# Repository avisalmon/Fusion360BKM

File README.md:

# Fusion360BKM

### Design a whole product with an AI that drives Fusion 360 for you: 3D parts, circuit boards a factory can make, and the case and production files that join them.

<!-- last-updated:start -->
**Last updated 20 November 2026** · 8 new lessons · [See what's new](docs/lessons_log.md)
<!-- last-updated:end -->

**Start page (Hebrew / English): https://avisalmon.github.io/Fusion360BKM/**

---

**Autodesk Fusion 360** is free for personal use and does 3D parts, electronics (schematics and boards) and the
fitting of one into the other. This repo is the best known method for working it **from a chat**: a small add-in
(`CopilotBridge`) runs inside Fusion and takes Python scripts over a local HTTP port; the AI in your editor writes
the script, runs it, reads back every body's measurements and a screenshot, and tells you what it sees. You keep
Fusion open beside the chat and watch the part appear.

Open the repo in VS Code with **Claude Code** or **GitHub Copilot** (Agent mode), type **"Tell me what to do"**
(or **"תגיד לי מה לעשות"**), and the chat:

* checks your computer and links the add-in into Fusion (one Fusion restart, once),
* asks what you want to make, writes a numbered spec in millimetres, and gets your OK,
* builds it in Fusion step by step, **verifying by numbers and by eye** after every run,
* exports STL for the printer, STEP for other CAD tools, F3D to keep,
* teaches as it goes, in Hebrew or English, and resumes where you stopped next time,
* pulls the newest version of this guide at the start of every session.

## Four stages

1. **Set up** (you, by hand): install [Fusion 360](https://www.autodesk.com/products/fusion-360/personal) and sign
   in; install [VS Code](https://code.visualstudio.com), [Git](https://git-scm.com/downloads), and an AI chat
   (Claude Code, or GitHub Copilot in Agent mode); in VS Code **Ctrl+Shift+P** -> **Git: Clone** -> paste
   `https://github.com/avisalmon/Fusion360BKM.git` -> **Open**. Every click: [docs/get_started.md](docs/get_started.md).
2. **Learn by hand, old school**: Avi Salmon's Fusion 360 course at
   [Babook](https://babook.co.il/courses/fusion360/) (Hebrew, seven video lessons: a coin, tweezers, a key, a
   vacuum-cleaner nozzle, a mug). Optional; the chat suggests the lesson that matches what you are about to build.
3. **The AI magic** (this repo): in the chat, type `Tell me what to do` / `תגיד לי מה לעשות`. The whole road is
   [docs/journey_checklist.md](docs/journey_checklist.md).
4. **Examples**: [examples/](examples/README.md), each with its scripts, files, pictures, what was verified, and what it
   taught this guide: [a box from a paper note](examples/06_sketched_box/README.md), three circuit boards, and the demo
   product below.

## Three tracks (and a fourth coming)

* **3D parts**: from words, a hand sketch or a real object, to a spec in mm, a script, checks, and STL to print.
* **Circuit design**: the circuit in words, a schematic, a placement *you* review, routing, then three layers of
  checks (Fusion's, ours against JLCPCB's limits, a simulated factory that reads the Gerbers) and one summary page
  per board with the zip to upload. Boards [10](examples/10_led_switch_board/index.html),
  [11](examples/11_blinker_555/index.html), [12](examples/12_tiny_arcade/index.html).
* **A whole product**: the board in 3D (every part's model comes from the library), a case designed around it and
  proven by intersecting every printed part with every part, screw, battery and cable, and a production package:
  STL, Gerbers, the assembly as STEP and `.f3d`, assembly steps, one bill of materials for everything. The demo:
  **[Tiny Arcade](examples/12_tiny_arcade/index.html)**, an ESP32 game board in a rounded handheld with a power
  bank inside (an example for learning, not for production).
* **Software** (coming later): the code that runs on the board, as part of the product.

## The part library

**[library/](library/index.html)**: real parts from a real shelf, each a full library cell (photos, pins checked on
the part, a footprint and symbol checked in Fusion, a 3D model). Every user keeps their own; Avi's is public, as the
example of what a library should look like. **Take one, give back two:** borrow a part from Avi's shelf today
instead of waiting for AliExpress, and order two that come back to him.

## What's in the box

```
index.html                 The start page (GitHub Pages), Hebrew + English
CLAUDE.md                  The AI's standing rules for this repo
.claude/skills/            9 playbooks: design-with-fusion, setup-fusion-bridge, fusion-modeling, fusion-files,
                           sketch-to-design, fusion-mentor, fusion-electronics, build-example, publish-to-github
.github/skills/            The same playbooks for GitHub Copilot (generated, kept identical by a test)
.github/copilot-instructions.md, AGENTS.md   Generated instructions + an index of every skill
CopilotBridge/             The Fusion add-in: HTTP server + helpers in millimetres (sketch, extrude, revolve,
                           fillet, shell, holes, patterns, parameters, export, screenshot)
scripts/fusion.py          One tool: doctor | install | launch | ping | new | run | exec | info | shot | export | dialog
scripts/fusion_dialog.ps1  Reads and clicks Fusion's modal dialogs when they block the bridge
templates/parametric_box/  A known-good start: a shelled box with a lid, eight parameters, verified
examples/                  Built from the chat, with evidence: 06_sketched_box (from a paper note); boards
                           10, 11 and 12; 12_tiny_arcade is a whole product with its production package
library/                   The part library: one folder per owner, one per part; index.html is its page
                           (scripts/library_page.py)
my_designs/                YOUR work (git-ignored, so updates never touch it)
exports/                   STL / STEP / F3D / PNG output (git-ignored)
docs/                      Setup, the journey, architecture, the Fusion reference, procedures, gotchas, what's new
```

## By hand, without the AI

```powershell
python scripts\fusion.py doctor                             # what is there, what is missing, the next command
python scripts\fusion.py install                            # link the add-in into Fusion (then restart Fusion once)
python scripts\fusion.py launch                             # start Fusion and wait for the bridge
python scripts\fusion.py ping                               # {"fusion": "2706.1.14", "bridge": "0.1.1", "doc": ...}
python scripts\fusion.py run templates\parametric_box\design.py
python scripts\fusion.py shot exports\box.png               # a picture of the viewport
python scripts\fusion.py new my_part                        # my_designs\my_part\design.py from the template
python scripts\fusion.py export my_part                     # STL (per body + whole), STEP, F3D into exports\
```

`scripts/fusion.py` needs only Python's standard library. The repo's own checks (`pytest`, `ruff`) use a virtualenv:
`python -m venv env` then `.\env\Scripts\python.exe -m pip install -r requirements-dev.txt`.

**What the setup is, in one paragraph.** Fusion must be running (minimised is fine) and signed in. The add-in is
linked into Fusion's AddIns folder and starts with Fusion; it listens on `127.0.0.1:8787` only. The chat sends a
Python script, the add-in runs it on Fusion's main thread, and sends back printed output, a `result` value and any
traceback. It is not an MCP server (a thin MCP wrapper over the same calls is possible later). A modal dialog in
Fusion blocks everything until somebody clicks it; `fusion.py dialog` can. Details: [docs/architecture.md](docs/architecture.md).

## Honest status

Tested on Windows 11 with Fusion 2706.1.14: `doctor`, `install` (as a junction), `launch` (a cold start, bridge up
in 35 s), `ping`, the template built through the bridge with its measurements read back and its screenshot
described, exports (STL, STEP, F3D), opening `.f3d` / STEP / STL, editing an opened design's timeline, and clearing
the update and *Active Sessions* dialogs. The first example is real: a hand-drawn paper note became a verified tray
in one run ([examples/06_sketched_box](examples/06_sketched_box/README.md)). The repo checks itself (ruff, tests,
skills in sync) and CI has been green on every push; the start page is served at the Pages URL above. Not yet: the
course's five examples, electronics, a printed part, a fresh clone on another computer, GitHub Copilot end to end,
macOS. See [docs/blueprint_roadmap.md](docs/blueprint_roadmap.md) and [docs/backlog.md](docs/backlog.md).

## License

[MIT](LICENSE). Use it, change it, teach with it.

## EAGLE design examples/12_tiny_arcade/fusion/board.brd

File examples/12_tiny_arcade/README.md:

# 12 Tiny Arcade: a game board from the owner's own parts, then its 3D model and its box

The Single Button kit ([SingleButtonKitBKM](https://github.com/avisalmon/SingleButtonKitBKM): an ESP32, a
0.96 inch screen, a button and a buzzer on a breadboard) as a small circuit board with six buttons: A, B and
a direction pad. Every part comes from the owner's library ([library/avi_salmon](../../library/README.md)),
real parts from his store with their pins confirmed on the part. The kit's pins are kept, so its programs
(Flappy) run unchanged. One flow: **board, then the board in 3D, then a 3D-printed box**, with two reviews
by the owner: the placement, and the printing concept.

Status: in progress. The board is done: the owner's placement (2026-11-19), routed on two layers with no
vias; Fusion's checks, our checks and the simulated factory all pass with 0 errors; the factory files are made
([summary page](index.html)). The board is in 3D, each part from its library model. The case (a rounded
handheld, the power bank inside, the board open on top) is agreed by the owner, and its production package is
made: STL files to print, the design (.f3d), the assembly (.step) with its screws and its cable, a true-size
paper template, assembly steps, and a bill of materials for everything (2026-11-20). **An example for learning,
not made for production** (the owner's word): it is not printed or ordered, and the bank is the owner's size,
100 x 70 x 15 mm.

| Part | Pin on the ESP32 | Note |
|---|---|---|
| screen SCL / SDA, VCC, GND | G22 / G21, 3V3, GND | the kit's pins |
| buzzer + / - | G23 / GND | the kit's pin |
| A, B | G4, G13 | A is the kit's one button |
| UP, DOWN, LEFT, RIGHT | G33, G26, G25, G32 | chosen so the four tracks reach the direction pad without crossing |

Each button's other contact goes to GND; the program turns on the pin's internal pull-up (released 1,
pressed 0), so there are no resistors. Pins avoided: 0, 2, 5, 12, 15 (they decide how the ESP32 starts),
1 and 3 (USB serial), 6-11 (flash), 34-39 (input only, no internal pull-up).

## Parts (the owner's library)

| Ref | Part | Library |
|---|---|---|
| U1 | ESP32 DevKitC, 38 pins | [esp32_devkitc_38](../../library/avi_salmon/esp32_devkitc_38/part.json) |
| DISP1 | OLED 0.96 inch, I2C, 4 pins | [oled_096_i2c](../../library/avi_salmon/oled_096_i2c/part.json) |
| BZ1 | buzzer TMB12A03 | [buzzer_tmb12a03](../../library/avi_salmon/buzzer_tmb12a03/part.json) |
| SW1-SW6 | tact switch 6 x 6 mm | [tact_switch_6x6](../../library/avi_salmon/tact_switch_6x6/part.json) |

## Build

```powershell
python scripts\fusion.py run examples\12_tiny_arcade\circuit.py 300   # 1. schematic (new design)
python scripts\fusion.py run examples\12_tiny_arcade\board.py 300     # 2. outline, holes, placement; the owner reviews
python scripts\fusion.py run examples\12_tiny_arcade\route.py 300     # 2b. tracks, once the owner agrees
python scripts\fusion.py run examples\12_tiny_arcade\factory.py 600   # 3. Fusion's checks, save, export, Gerbers
python scripts\pcb_check.py examples\12_tiny_arcade\fusion\board.brd  # 4. our board check, no Fusion needed
python scripts\factory_check.py examples\12_tiny_arcade\factory       # 5. the simulated factory
python scripts\fusion.py run examples\12_tiny_arcade\board3d.py 300   # 6. the board in 3D, the parts on it
python scripts\fusion.py run examples\12_tiny_arcade\case.py 900      # 7. the case, its checks, the production files
python scripts\board_summary.py examples\12_tiny_arcade              # 8. the summary page: board, case, production
```

The first placement proposal, then the owner's (a console: A and B left, the screen in the middle, the
direction pad right), then the routed board: top copper red, bottom blue.

The board in 3D, each part built from the model in its library record (boxes and cylinders, every size
with its source):

## The case (`case.py`)

The owner's brief (2026-11-20): rounded, modern, the power bank under the board, and the screen and buttons
left open so they are pressed and seen directly. Version 1 was a closed box with button caps; the owner
called it "too boxy", so it now lives only in git history. Version 2 is a rounded handheld, 140 x 82 mm and
21 mm thick to the deck, with the board on top (36 mm to the top of the buzzer). It is printed as two
parts, each flat and with no supports:

* **Body**: a rounded shell: corners of radius 30 seen from above, and a rounded bottom edge. The bank lies
  inside it, and ribs stop it sliding. The two ends are grips, so the thumbs land on A and B (left) and on
  the direction pad (right). A port bay in the left end shows the bank's ports and lights. It prints open
  side up.
* **Deck**: the lid. The board sits on four posts on it (4 x M3 x 8 from above, through the board's holes),
  inside a raised rim that guards its edges and is open at the ESP32's USB. Four M3 x 10 screws through the
  deck into columns in the grips hold the deck and the body together. It prints flat side down.

The bank sits 5 mm right of the centre, so the left grip has room for a short cable (10 cm): its USB-A plug in
the bank's left end, up through a slot in the deck, to the ESP32's micro-USB at the gap in the rim. The cable is
modelled too (blue in the pictures), so the fit check proves there is room for it. The port bay in the left end
reaches the bank's charging port and shows its lights.

The board, its parts and the bank are in the design as reference bodies, and the script intersects every
printed part with every one of them: all 0 mm3. Version 1 proved the check: a part moved 0.5 mm into
another gave exactly the expected volume.

### Production (`production/`, written by `case.py`)

| File | What it is |
|---|---|
| [tiny_arcade_case_body.stl](production/tiny_arcade_case_body.stl), [tiny_arcade_case_deck.stl](production/tiny_arcade_case_deck.stl) | the two printed parts, in mm, the right way up for the bed |
| [tiny_arcade_case.f3d](production/tiny_arcade_case.f3d) | the case's design in Fusion, the whole timeline (re-opened once to prove it: 8 components, 37 bodies) |
| [tiny_arcade_assembly.step](production/tiny_arcade_assembly.step) | the whole assembly (case, board, parts, bank, cable, the 8 screws) for any CAD program |
| [template_top_1to1.svg](production/template_top_1to1.svg) | the top at true size: print it on paper at 100 %, cut it out, hold it, try the buttons with your thumbs |
| [BOM.csv](production/BOM.csv) | everything to buy or make: the PCB, the 9 parts, the 2 printed parts, 8 screws, the bank, the cable |
| [production.json](production/production.json) | the assembly steps, the fit checks and the thumb distances, for the summary page |

Print in PLA, 0.2 mm layers, 4 walls, 20 % infill, no supports. Lay the body open side up and the deck flat side
down; both are already the right way up in the STL. Assembly (with the [exploded view](media/case_exploded.png)):
solder the board; screw it onto the deck (4 x M3 x 8); lay the bank in the body, ports to the left; screw the
deck onto the body (4 x M3 x 10, into the grips), the cable's far end through the deck's slot first; plug
it into the ESP32.

The thumbs: A and B sit 35-37 mm in from the left end; the direction pad's centre sits about 48 mm in from the
right end (LEFT 57 mm, RIGHT 39 mm). The pad is 11 mm further in from its end than A and B are from theirs, because
the board is centred in the case. Whether that is comfortable is for a hand to say: the paper template first.

## Status

| Step | Done |
|---|---|
| Parts: the owner's library, each part's symbol and footprint placed in Fusion and read back | 2026-11-19, Fusion 2706.1.17 |
| Schematic from the chat: 9 parts, 10 supply symbols, 11 nets; the netlist read back equal to the intent; looked at ([media/schematic.png](media/schematic.png)): no wire crosses another | 2026-11-19 |
| The ESP32's GND pins (the "power" kind, no wire) on the board's GND signal | 2026-11-19: pads 14, 20 and 26 read back in GND |
| Placement, first proposal: 86 x 64 mm, four M3 holes | 2026-11-19: placed and looked at ([media/placement_proposal.png](media/placement_proposal.png)) |
| Placement reviewed and moved by the owner in Fusion (a console layout), read back into `board.py`; B moved 1.5 mm off the corner screw, agreed | 2026-11-19 ([media/placement_owner.png](media/placement_owner.png)) |
| Routed (`route.py`): two layers, no vias; the direction pins swapped so no tracks cross (UP G33, DOWN G26, RIGHT G32) | 2026-11-19: 0 unrouted, no copper off the two layers, looked at ([media/board.png](media/board.png)) |
| Fusion's checks | 2026-11-19: board check 0 errors; ERC 5 findings, unused ESP32 input pins (EN, SVP, SVN, G34, G35), approved in `checks.json` with that reason, confirmed by the owner 2026-11-20 |
| Our board check (`pcb_check.py`) and the simulated factory (`factory_check.py`) | 2026-11-19, after a clean rebuild in a new design: 0 errors; the netlist equal to the intent; the bare-board e-test equal to the schematic (11 nets, no opens, no shorts). 2026-11-20: 0 warnings, once `pcb_check.py` learned that our library's parts carry their 3D model in part.json |
| Saved to the Fusion cloud (project "Tiny Arcade"), factory files | 2026-11-19 |
| The board in 3D, with the parts as 3D objects (`board3d.py`: each part's model from its library part.json, at its place on Fusion's 3D board) | 2026-11-19: built; each part's bounding box read back over its footprint; looked at ([media/board3d.png](media/board3d.png)). Heights above the board's underside: ESP32 8.7 mm (soldered straight on, 2026-11-20; it was 17.2 on female headers), buzzer 11.0, screen 6.6, buttons 6.5 (the 5 mm button is assumed): **to be measured** |
| The ESP32 soldered straight onto the board (no sockets), the owner's choice | 2026-11-20: `board3d.py` and `case.py` model it so; the ESP32's top is 7.2 mm above the board (from its model, not measured) |
| Printing concept: a power bank underneath, a short cable outside (the owner's direction); bank 100 x 70 x 15 mm (the owner's working size; the AliExpress listing's drawing says 93 x 63.5 x 14) | 2026-11-20 |
| The case, version 1 (a closed box, button caps) | 2026-11-20: built, 0 mm3 against every part; the owner: "too boxy" |
| The case, version 2 (`case.py`): a rounded handheld, the board open on top, the bank inside; body and deck | 2026-11-20: built in Fusion 2706.1.17; looked at from five views (media/case_v2*.png); **agreed by the owner** ("I like it"); the bank, the buttons, the screen and the buzzer are assumed sizes, **to be measured** |
| Production package (`production/`): STLs, .f3d (re-opened: 8 components, 37 bodies), .step, true-size template, BOM for everything, assembly steps, exploded view; the 8 screws and the cable modelled | 2026-11-20: 503 pairs intersected (printed parts and screw heads against everything, the cable included; shanks against the board and its parts): 0 mm3; the template rendered and looked at |
| The thumbs: comfortable to hold and press | measured on the model only (above); not tried by hand: an example, not printed |
| Printed, fitted | not planned: an example for learning (the owner, 2026-11-20) |

## What it taught this repo (so far)

* **Check what a command added, not only what it was asked to add.** Every ADD from a local library left
  one more copy of the part at the sheet's edge, which took the next name the script wanted. `sch_place`
  now ends the ADD (`EDIT .s1`) and fails if anything else appeared (gotcha 48).
* **Our check learned the supply pins**: an ESP32 pin named GND@14 of direction "pwr" joins GND with no
  wire; Fusion's board did, our check's schematic did not, so they disagreed. `pcb_check.py` now joins such
  pins by name, as EAGLE does.
* **Silkscreen stops short of the pads** in generated footprints (a square pad 1 reaches out to its corners).
* **One pin on two pads** (the tact switch's joined legs) and **GND pins that join by name**: the board's
  signal has them, the schematic's nets do not list them.

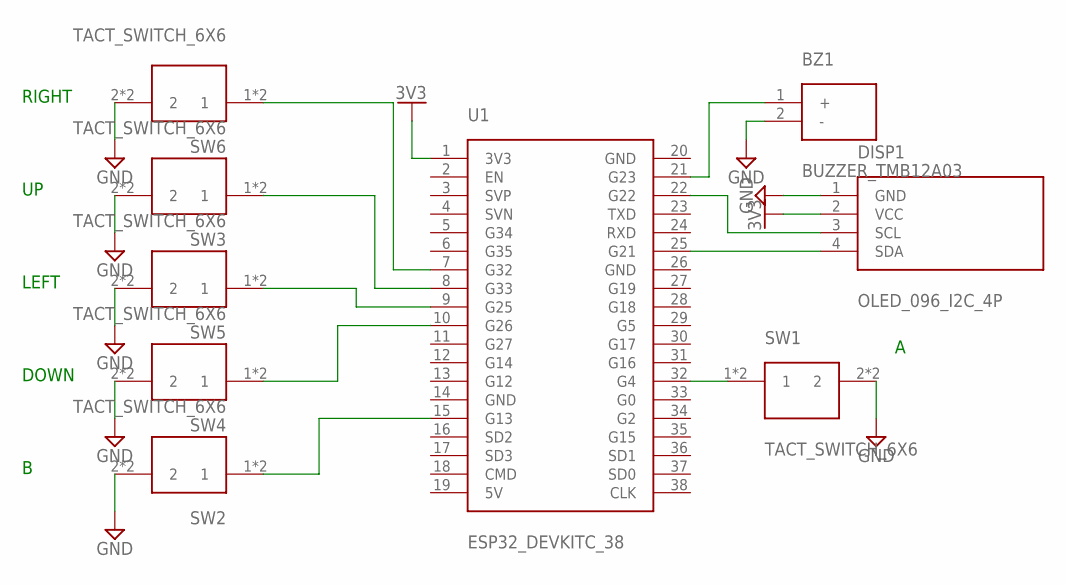
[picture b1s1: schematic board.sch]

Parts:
BZ1: BUZZER_TMB12A03
DISP1: OLED_096_I2C_4P
SW1, SW2, SW3, SW4, SW5, SW6: TACT_SWITCH_6X6
U1: ESP32_DEVKITC_38

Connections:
3V3: DISP1.2 (VCC), U1.1 (3V3)
BTN_A: SW1.1, SW1.3 (1), U1.32 (G4)
BTN_B: SW2.1, SW2.3 (1), U1.15 (G13)
BTN_DOWN: SW4.1, SW4.3 (1), U1.10 (G26)
BTN_LEFT: SW5.1, SW5.3 (1), U1.9 (G25)
BTN_RIGHT: SW6.1, SW6.3 (1), U1.7 (G32)
BTN_UP: SW3.1, SW3.3 (1), U1.8 (G33)
BUZZER: BZ1.1 (+), U1.21 (G23)
GND: BZ1.2 (-), DISP1.1 (GND), SW1.2, SW1.4 (2), SW2.2, SW2.4 (2), SW3.2, SW3.4 (2), SW4.2, SW4.4 (2), SW5.2, SW5.4 (2), SW6.2, SW6.4 (2), U1.14 (GND), U1.20 (GND), U1.26 (GND)
SCL: DISP1.3 (SCL), U1.22 (G22)
SDA: DISP1.4 (SDA), U1.25 (G21)

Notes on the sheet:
RIGHT
LEFT
DOWN

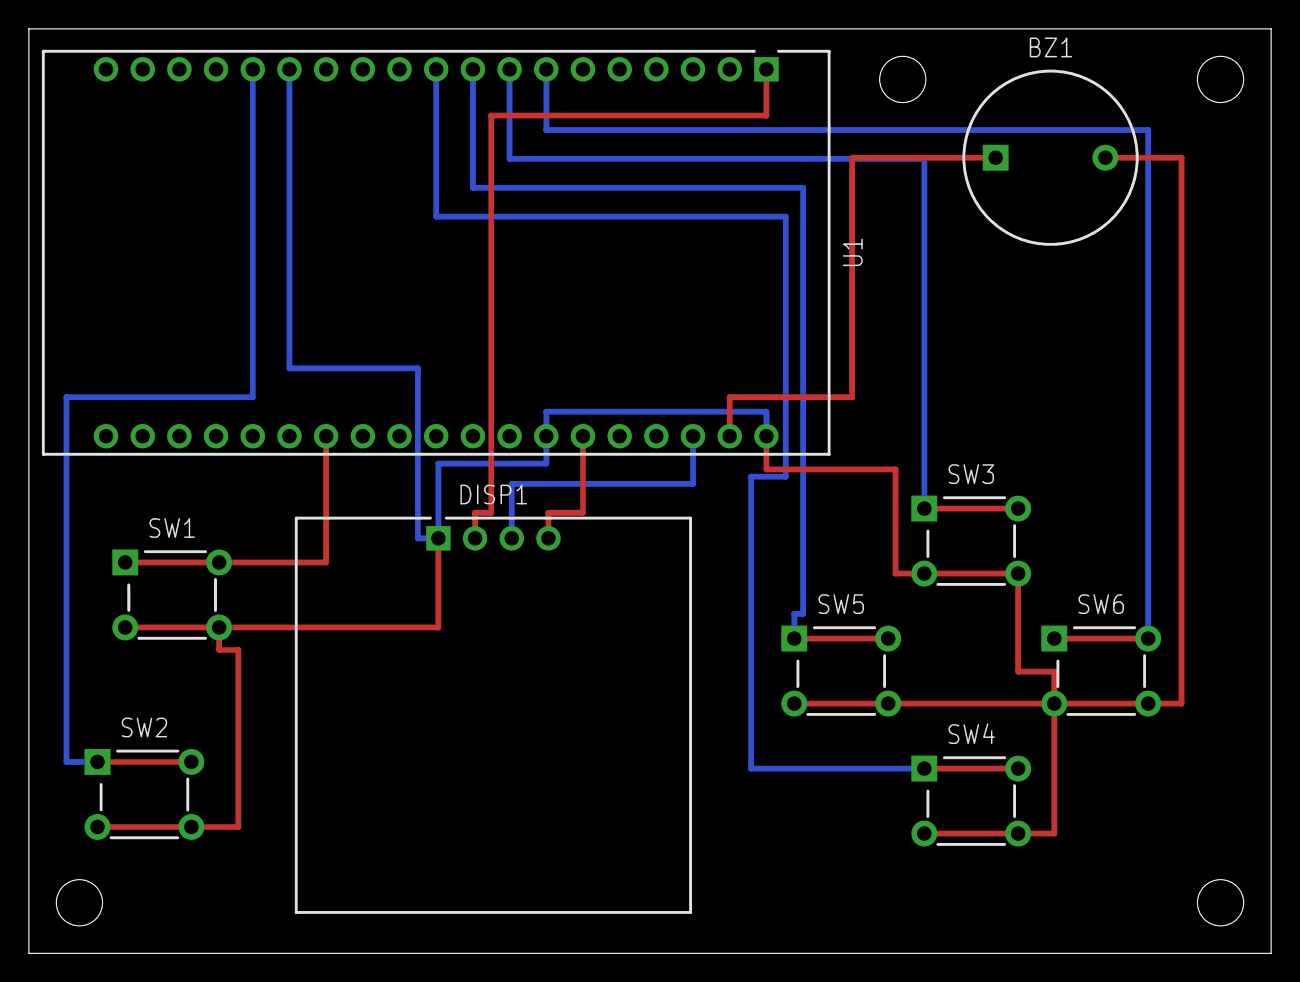
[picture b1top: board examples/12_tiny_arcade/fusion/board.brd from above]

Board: 2 copper layers, 86.0 x 64.0 mm, 9 parts (0 on the bottom side), 11 nets.

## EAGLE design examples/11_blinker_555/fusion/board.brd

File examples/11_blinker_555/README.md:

# 11 Blinker 555: the first board with a chip

A 555 timer blinks a red LED about once a second, from a 9 V battery. Board 10 walked the road once with
nets of two pins; this board's nets join three, four and five pins, it has a chip with eight pins, a part with
a plus and a minus (the 10 uF capacitor), and a schematic that uses power symbols. Not from a Babook lesson
(the 3D course is on Babook, https://babook.co.il/courses/fusion360/).

Status: in progress. The owner reviewed and moved the placement by hand on 2026-11-18, and the board was
routed again on 45 x 31 mm, saved, and its factory files made. Every check passes (0 errors, 0 warnings) with
the findings the owner approved, each with its reason, in `checks.json`: [ready to order the bare
board](index.html). Not yet: the order itself, soldering, a blinking LED.

```text
+9V -- R1 1k -- DIS -- R2 68k -- THR -- C1 10uF -- GND          U1 = NE555: pin 7 DIS, pins 6 and 2 THR
U1 pin 3 (OUT) -- R3 680R -- D1 red LED -- GND                  pin 5 CV -- C2 10nF -- GND
pins 4 (reset) and 8 (V+) to +9V; pin 1 to GND
```

Blink rate: f = 1.44 / ((R1 + 2 R2) C1) = 1.44 / (137 kohm x 10 uF) = 1.05 Hz, the LED on about 51 % of
each period (the textbook formula; the real rate depends on C1's tolerance, 20 %). LED current:
(9 V - 1.7 V out drop - 2 V LED) / 680 ohm, about 8 mA (rough: the NE555's high output sits 1.4 to 2 V
below +9V).

## Parts (all from Fusion's own libraries, found with `scripts/fusion_parts.py`)

| Ref | Part, as `ADD` names it | Value | Why this one |
|---|---|---|---|
| J1 | `B2B-XH-A@Connector` | B2B-XH-A (fixed) | the JST XH 2-pin header from board 10, for the 9 V battery clip's leads |
| U1 | `NE555_DIP@IC_Clock-Timing` | NE555_DIP (fixed) | Texas Instruments NE555P, DIP-8, PART_STATUS Active, 3D model |
| R1, R2, R3 | `RESISTOR_AXIAL-10.16MM-PITCH@Tinkercad` | 1k, 68k, 680R | the axial resistor from board 10 |
| C1 | `10UF-POLAR-RADIAL-2.5MM-25V-20%@SparkFun-Capacitors` | 10uF | electrolytic, 25 V (above 9 V with margin), pins `+` (pad 1) and `-` (pad 2) |
| C2 | `CAPACITORCERAMIC-2.54MM@Tinkercad` | 10nF | ceramic, 2.54 mm pitch |
| D1 | `LED5MM@SparkFun-LED` | RED 5MM | the 5 mm LED from board 10 |
| P1-P4, G1-G5 | `+9V@Power_Symbols`, `GND@Power_Symbols` | +9V, GND | power symbols: schematic only, no footprint |

## Build

```powershell
python scripts\fusion.py run examples\11_blinker_555\circuit.py 180    # 1. schematic (new design)
python scripts\fusion.py run examples\11_blinker_555\board.py 180      # 2. outline, holes, placement; the owner reviews
python scripts\fusion.py run examples\11_blinker_555\route.py 180      # 2b. tracks, once the owner agrees
python scripts\fusion.py run examples\11_blinker_555\factory.py 300    # 3. Fusion's checks, save, export, Gerbers
python scripts\pcb_check.py examples\11_blinker_555\fusion\board.brd  # 4. our board check, no Fusion needed
```

The board, 45 x 31 mm, with the owner's placement: top copper red, bottom blue, four M3 holes (the
fourth beside R2, which saved an empty strip along the top). Pins 4 and 8 (+9V) and pins 2 and 6 (THR) both cross under the 555, diagonally, one link on each layer; no vias.

## Status

| Step | Done |
|---|---|
| Parts found in Fusion's libraries (NE555 Active with a 3D model, the electrolytic with marked + and -) | 2026-11-18, Fusion 2706.1.17 |
| Schematic from the chat: 8 parts, 9 power symbols, 7 nets; the netlist read back equal to the intent on the first run; looked at ([media/schematic.png](media/schematic.png)): one crossing (pin 6 over pin 7's wire, no dot), every other join a dot | 2026-11-18 |
| Electrical rules check (ERC) | ran 2026-11-18: one finding, "POWER pin U1 V+ connected to +9V" (the 555's supply pin is named V+, its net +9V); approved by the owner with that reason, 2026-11-18, in `checks.json` (`FUSION-ERC`) |
| Board, first try: 50 x 40 mm, routed on both layers | 2026-11-18: 0 unrouted, no copper off the two layers; Fusion's board check 0 errors; looked at ([media/board.png](media/board.png)) |
| Placement reviewed and moved by the owner in Fusion, agreed; routed again (`route.py`); board shrunk to 45 x 31 mm with the fourth hole beside R2 | 2026-11-18: 0 unrouted, Fusion's board check 0 errors, looked at ([media/board.png](media/board.png)) |
| Our board check (`pcb_check.py`) on the export | 2026-11-18, again on the 45 x 31 board: 0 errors; the netlist equals the intent in `checks.json`; 8 silkscreen warnings (thin lines in the Tinkercad resistor and NE555 footprints, marks near pads), approved by the owner with reasons, 2026-11-18: 0 errors, 0 warnings, 8 approved |
| GND copper pour | not yet |
| Saved to the Fusion cloud, Gerbers and drill file, `factory_check.py` | 2026-11-18, after a clean rebuild (circuit, board, route) in a new design, once the owner had freed editable documents: saved, 10 factory files, `factory_check.py` 0 errors, the bare-board e-test equal to the schematic (7 nets, no opens, no shorts); 13 warnings (4 screw holes plated, silkscreen of the library footprints, no LCSC numbers: a hand-soldered kit) approved by the owner with reasons: 0 errors, 0 warnings, 13 approved |
| Ordered, soldered, blinking | not yet (human steps) |

## What it taught this repo (so far)

* **A fix verified on the wrong case.** Gotcha 21 said `SET CONFIRM YES` answers "Part J1 has no user
  definable value. Change it anyway?"; it was checked on D1, which never asks. On J1 the question still came.
  Now `sch_place` reads `deviceset.userValue` first and refuses, instead of hanging Fusion; fixed-value parts
  (J1, U1) simply keep their library value.
* **Power symbols ask for their name** on every placement (gotcha 35). A value inside the ADD command made
  Fusion report an internal error; what works is a watcher: `sch_place` starts `fusion_dialog.ps1` in the
  background, which waits for that one "Value" box and clicks OK, and leaves every other dialog alone.
* **A net of many pins** is several `NET` wires with the same name; GND here is five pins and five symbols.
* **Some crossings cannot be avoided**: with the 555's pins in their fixed order, pins 2 and 6 must meet
  while pin 7 lies between them. A crossing without a dot is not a connection; the netlist check proves it.
* `scripts/fusion_window_shot.ps1` takes the screenshot `fusion.py shot` cannot take in the electronics
  editors (gotcha 18).
* **The bottom copper is layer 304, not 16** (gotcha 37). The first routing put GND and a THR link on an inner
  layer: Fusion showed zero-length airwires at every pad, while the exported file and our check looked perfect.
* **`ROTATE =R90 R1` turns nothing**: R1 is read as an angle (gotcha 36). **Route pad to pad**: tracks ending
  on another track's corner raised Fusion's "unexpected condition" box (gotcha 38).

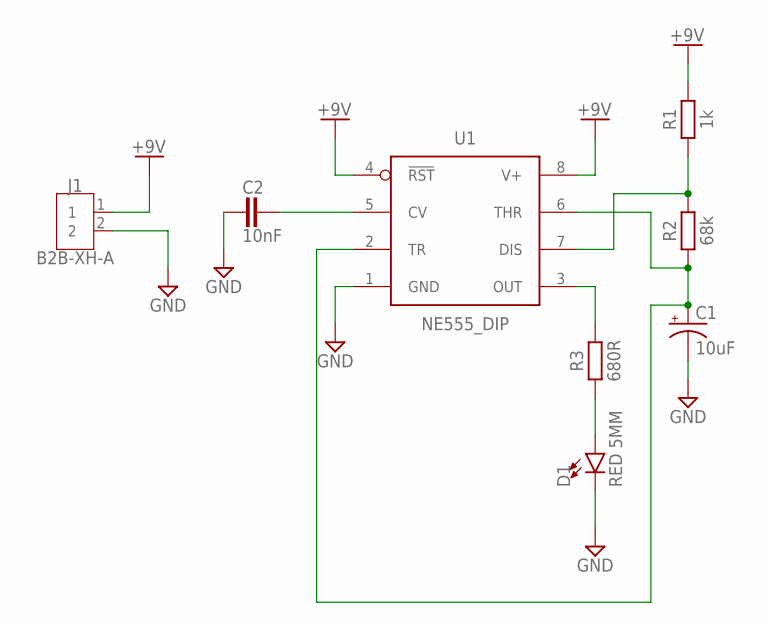
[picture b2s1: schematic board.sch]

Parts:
C1: 10uF; CPOL-RADIAL-2.5MM-5MM
C2: 10nF; CAP-THRU-2.54MM
D1: RED 5MM; LED_5MM
J1: B2B-XH-A
R1: 1k; RESAD1016W63L850D250B
R2: 68k; RESAD1016W63L850D250B
R3: 680R; RESAD1016W63L850D250B
U1: NE555_DIP; DIP826W53P254L959H508Q8B

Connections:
+9V: J1.1, R1.2, U1.4 (!RST), U1.8 (V+)
CV: C2.1, U1.5 (CV)
DIS: R1.1, R2.2, U1.7 (DIS)
GND: C1.2 (-), C2.2, D1.K (C), J1.2, U1.1 (GND)
LED_A: D1.A, R3.1
OUT: R3.2, U1.3 (OUT)
THR: C1.1 (+), R2.1, U1.2 (TR), U1.6 (THR)

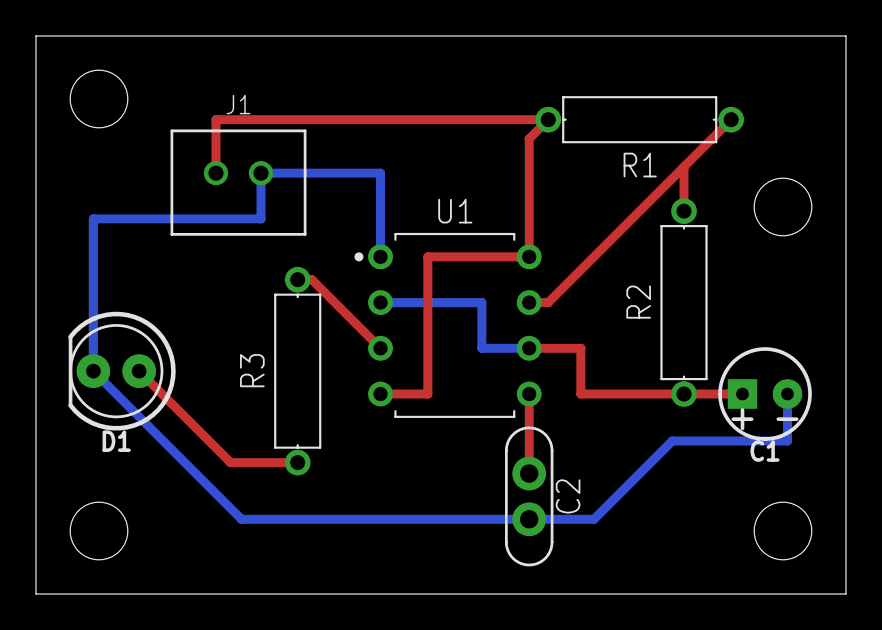
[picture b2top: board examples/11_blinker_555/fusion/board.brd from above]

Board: 2 copper layers, 45.0 x 31.0 mm, 8 parts (0 on the bottom side), 7 nets.

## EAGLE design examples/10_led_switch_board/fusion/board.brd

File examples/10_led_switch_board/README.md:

# 10 LED switch board: the first board from the chat

A battery connector, a slide switch, a resistor and an LED on a small two-layer board, then a printed case
around it. The smallest real board that walks the whole road once: parts from the library, schematic, electrical
check, board, design-rule check, factory files, the board in 3D, a case that fits. Not from a Babook lesson: it
opens the electronics stage (the 3D course is on Babook, https://babook.co.il/courses/fusion360/).

Status: in progress (schematic, board, every check and the factory files done; order, 3D board and case next).

```text
J1 (battery, JST XH 2-pin) --VBAT-- SW1 (slide, SPDT) --VSW-- R1 100R --LED_A-- D1 (5 mm LED) --GND-- J1
```

## Parts (all from Fusion's own libraries, all with a 3D model; found with `scripts/fusion_parts.py`)

| Ref | Part, as `ADD` names it | Value | Why this one |
|---|---|---|---|
| J1 | `B2B-XH-A@Connector` | B2B-XH-A | JST XH, top entry, MPN `B2B-XH-A(LF)(SN)`, status ACTIVE; the usual battery-pack plug |
| SW1 | `SWITCH-SPDT-PTH-11.6X4.0MM@SparkFun-Switches` | SPDT | SparkFun COM-00102 slide switch, through-hole; its second throw (pin S) stays free. The TE `1825159-1@Switches` was rejected: "pending discontinuance", and its prefix is U |
| R1 | `RESISTOR_AXIAL-10.16MM-PITCH@Tinkercad` | 100R | axial, 10.16 mm pitch. Fusion's own `R-USAXIAL-7.2MM-PITCH_@Resistor` crashes the ADD command (gotcha 22) |
| D1 | `LED5MM@SparkFun-LED` | RED 5MM | 5 mm through-hole LED; pins A and C |

R1 = 100 ohm suits two AA cells (3 V) and a red LED: (3.0 - 2.0) V / 100 ohm = 10 mA.

**The board's summary page: [index.html](index.html)** (verdict, every check, the schematic and board drawn, every file;
generated by `python scripts\board_summary.py examples\10_led_switch_board`).

## Build and check

```powershell
python scripts\fusion.py run examples\10_led_switch_board\circuit.py 120   # 1. schematic (new design)
python scripts\fusion.py run examples\10_led_switch_board\board.py 120     # 2. board, on the same design
python scripts\fusion.py run examples\10_led_switch_board\factory.py 300   # 3. Fusion's checks, save, export, Gerbers
python scripts\pcb_check.py examples\10_led_switch_board\fusion\board.brd  # 4. our board check (no Fusion)
python scripts\factory_check.py examples\10_led_switch_board\factory       # 5. the simulated factory (no Fusion)
```

What is in the folder: `fusion/board.sch` + `board.brd` (Fusion's EAGLE export, what the checks read),
`checks.json` (the intended nets, the free pin, the accepted findings with reasons), `factory/` (the Gerber and
drill files from Fusion, the BOM and pick-and-place, previews; `board_gerbers.zip` is rebuilt by step 5).
How the checks work: [docs/procedures/board_checks_and_factory.md](../../docs/procedures/board_checks_and_factory.md).

What the factory receives, drawn from the Gerbers alone (top, then bottom as seen from below):

## Status

| Step | Done |
|---|---|
| Parts found in Fusion's libraries, each with a 3D model | 2026-11-16, Fusion 2706.1.17 |
| Schematic from the chat: 4 parts, 4 nets drawn as one visible loop, read back equal to the spec, looked at ([media/schematic.png](media/schematic.png)) | 2026-11-16 |
| Electrical rules check (ERC) clean: Fusion's ERC found 0 (first run: "SW1 has no value", "D1 has no value"; values added) | 2026-11-17 |
| Board: 30 x 20 mm outline, parts placed, two M3 holes, routed; 0 airwires read back and in Fusion's inspector, looked at ([media/board.png](media/board.png)) | 2026-11-16 |
| Fusion's board check clean (errors panel empty) | 2026-11-17 |
| Our board check (`pcb_check.py`, JLCPCB's limits): netlist equal to the intent, board equal to the schematic, all routed, 0 errors, 0 warnings, 3 approved (R1's library silkscreen) | 2026-11-17 |
| Factory files from a CAM job (9 Gerber layers, 1 drill file), checked outside Fusion (`factory_check.py`): outline 30 x 20 mm, 11 holes all accounted for, simulated electrical test equal to the schematic (no opens, no shorts), mask on every pad, smallest copper gap 0.606 mm; BOM, pick-and-place, zip | 2026-11-17 |
| Ordered from a fab (its own review, a real electrical test) | not yet (a human step: upload `board_gerbers.zip`) |
| 3D PCB, and a case around it | not yet |
| Soldered, lit; case printed and fitted | not yet (human steps) |

## What it taught this repo

* Electronics writes are EAGLE commands, checked by reading back (gotcha 17); a wrong library name places nothing.
* `VALUE` on a part with a fixed value asks a blocking question (gotcha 21); J1 keeps its library value (board 11
  showed that `SET CONFIRM YES` does not answer the question), so every
  part gets a value: the ERC calls a missing one an error, and the BOM needs it.
* A part whose technology is `_` crashes Fusion's ADD (gotcha 22); `fusion_parts.py` flags them.
* The board editor starts on a mil grid (gotcha 24); deleting through the API broke Fusion (gotcha 25).
* Fusion's router keeps its own rules: the corner it moved to 1.27 mm from the edge is its 1.02 mm Board Outline
  Clearance plus half the track (gotcha 26). It also refuses rule-breaking wires and holes without a word
  (gotcha 29), so Fusion staying quiet is not proof: our own check on the exported files is.
* `DRC` only opens Fusion's rule dialog (gotcha 27); *Check Design Rules* checks, but `Board.checked` never turns
  true (gotcha 32).
* Factory files need a saved design and land in an odd folder (gotcha 28); a rebuilt design saved under the same
  name made a twin (gotcha 30).
* The Gerbers showed what the design did not: thick silkscreen arcs are hatched with hairlines (gotcha 31), and the
  M3 holes go into the plated drill file (gotcha 33; approved: plated is fine for a screw).
* SparkFun's parts print their names 0.61 mm high, below the fab's 1.0 mm; `brd_name_size(1.0)` fixes them.
  Tinkercad's R1 draws 0.12 mm silkscreen lines touching its pads; approved for now, our own library (backlog
  E3.5) will fix it at the source.
* A schematic is for people: the first version joined the parts only by matching net labels, and the owner saw
  "just components spread around". Small circuits are drawn as visible wires, with corners chosen from the pins'
  read-back positions so no wire passes another pin; the netlist check catches a wrong join.

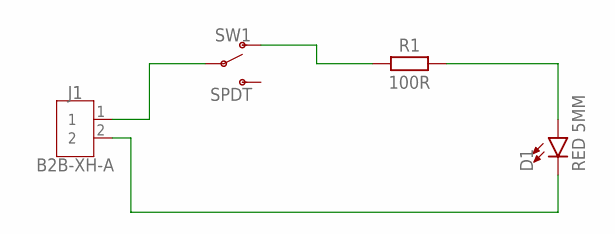
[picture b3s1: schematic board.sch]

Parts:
D1: RED 5MM; LED_5MM
J1: B2B-XH-A
R1: 100R; RESAD1016W63L850D250B
SW1: SPDT; SWITCH_SPDT_PTH_11.6X4.0MM

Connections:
GND: D1.K (C), J1.2
LED_A: D1.A, R1.2
VBAT: J1.1, SW1.2
VSW: R1.1, SW1.1 (O)

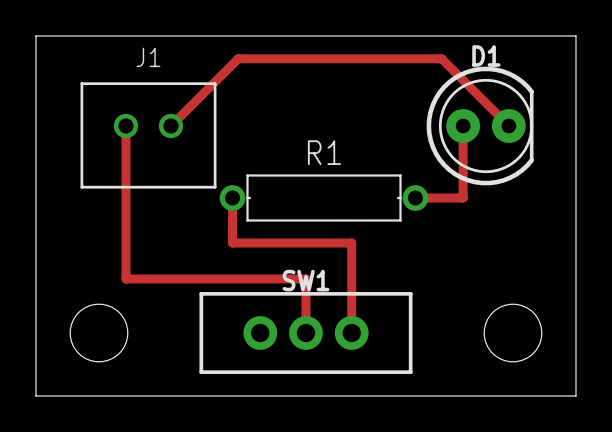
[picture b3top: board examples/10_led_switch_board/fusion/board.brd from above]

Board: 2 copper layers, 30.0 x 20.0 mm, 4 parts (0 on the bottom side), 4 nets.

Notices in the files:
parts and their libraries:
SparkFun-LED: Licensing: Creative Commons ShareAlike 4.0 International - https://creativecommons.org/licenses/by-sa/4.0
